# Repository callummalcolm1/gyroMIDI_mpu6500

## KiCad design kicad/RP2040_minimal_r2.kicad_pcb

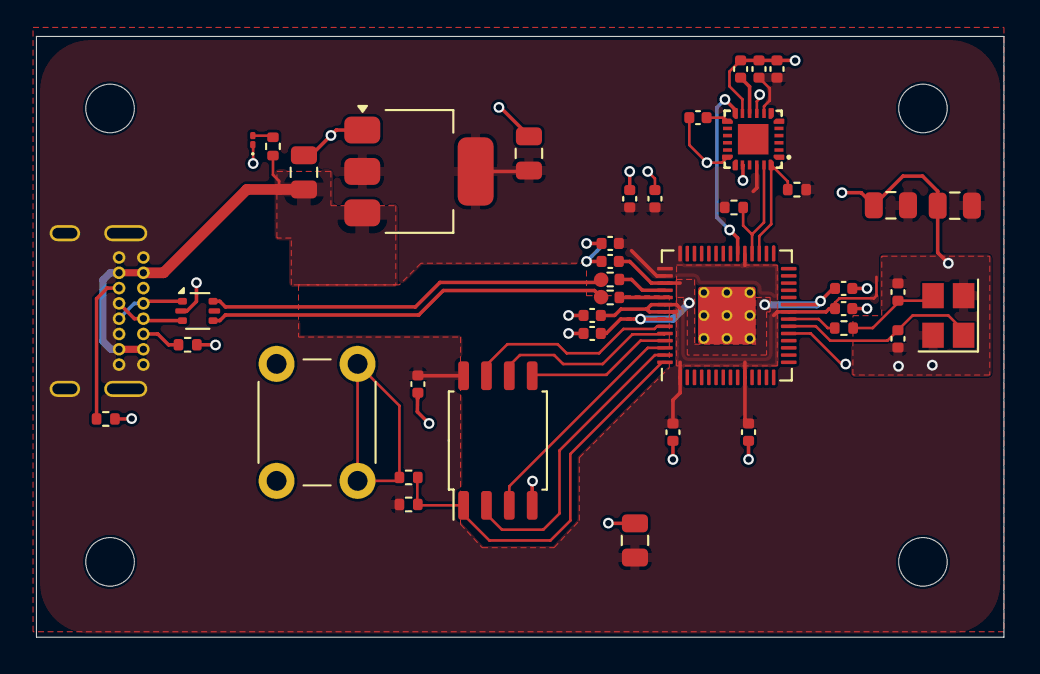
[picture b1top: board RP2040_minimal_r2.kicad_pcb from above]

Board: 2 copper layers, 53.8 x 33.4 mm, 45 parts (1 on the bottom side), 28 nets.

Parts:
C1: 0.1uF; C_0805_2012Metric
C1#2, C5, C6, C7, C9, C11, C12, C13, C14, C15, C16: 100n; C_0402_1005Metric
C2, C3: 15p; C_0402_1005Metric
C4: 2.2uF; C_0805_2012Metric
C4#2, C20: 1uF; C_0402_1005Metric
C8, C10: 1u; C_0402_1005Metric
C17, C18, C19: 10u; C_0805_2012Metric
D1: LED; LED_01005_0402Metric
H1, H2, H3, H4: MountingHole; MountingHole_2.7mm_M2.5
J5: USB_C_Receptacle_USB2.0_16P; USB_C_Receptacle_GCT_USB4085
R1, R5: 1k; R_0402_1005Metric
R2: DNF; R_0402_1005Metric
R3, R4: 27R; R_0402_1005Metric
R6, R7: 5.1K; R_0402_1005Metric
R8, R9: 4.7K; R_0402_1005Metric
R10: R; R_0402_1005Metric
SW1: SW_Push; SW_PUSH_6mm_H4.3mm
U1: MPU6500; QFN-24_L3.0-W3.0-P0.40-BL-EP
U2: W25Q128JVS; SOIC-8_5.23x5.23mm_P1.27mm
U3: RP2040; RP2040-QFN-56
U4: NCP1117-3.3_SOT223; SOT-223-3_TabPin2
U5: USBLC6-2SC6; SOT-666
Y1: ABM8-272-T3; Crystal_SMD_3225-4Pin_3.2x2.5mm

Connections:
+1V1: C6.1, C7.1, C8.1, U3.23 (DVDD), U3.45 (VREG_VOUT), U3.50 (DVDD)
+3V3: C1.1, C1#2.1, C4.1, C5.1, C9.1, C10.1, C11.1, C12.1, C13.1, C14.1, C15.1, C16.1, C17.1, C19.1, R2.1, R8.1, R9.1, U1.8 (VDDIO), U1.22 (nCS), U2.8 (VCC), U3.1 (IOVDD), U3.10 (IOVDD), U3.22 (IOVDD), U3.33 (IOVDD), U3.42 (IOVDD), U3.43 (ADC_AVDD), U3.44 (VREG_IN), U3.48 (USB_VDD), U3.49 (IOVDD), U4.2 (VO)
D+: R3.1, U5.4 (I/O2)
D-: R4.1, U5.6 (I/O1)
GND: C1.2, C1#2.2, C2.2, C3.2, C4.2, C4#2.1, C5.2, C6.2, C7.2, C8.2, C9.2, C10.2, C11.2, C12.2, C13.2, C14.2, C15.2, C16.2, C17.2, C18.2, C19.2, C20.1, D1.1 (K), J5.A1 (GND), J5.A12 (GND), J5.B1 (GND), J5.B12 (GND), J5.S1 (SHIELD), R6.1, R7.1, SW1.1, U1.9 (SDO/AD0), U1.11 (FSYNC), U1.18 (GND), U1.20 (RESV), U2.4 (GND), U3.19 (TESTEN), U3.57 (GND), U4.1 (GND), U5.2 (GND), Y1.2, Y1.4
INT: U1.12 (INT), U3.34 (GPIO22)
unnamed: C3.1, R5.2, Y1.3
unnamed: D1.2 (A), R10.2
unnamed: J5.A5 (CC1), R7.2
unnamed: J5.B5 (CC2), R6.2
unnamed: J5.A6 (D+), J5.B6 (D+), U5.3 (I/O2)
unnamed: J5.A7 (D-), J5.B7 (D-), U5.1 (I/O1)
unnamed: R1.2, SW1.2
unnamed: C20.2, U1.10 (REGOUT)
unnamed: C4#2.2, U1.13 (VDD)
unnamed: R4.2, U3.46 (USB_DM)
unnamed: R3.2, U3.47 (USB_DP)
QSPI_SCLK: U2.6 (CLK), U3.52 (QSPI_SCLK)
QSPI_SD0: U2.5 (DI(IO0)), U3.53 (QSPI_SD0)
QSPI_SD1: U2.2 (DO(IO1)), U3.55 (QSPI_SD1)
QSPI_SD2: U2.3 (IO2), U3.54 (QSPI_SD2)
QSPI_SD3: U2.7 (IO3), U3.51 (QSPI_SD3)
QSPI_SS: R1.1, R2.2, U2.1 (~CS), U3.56 (QSPI_SS)
SCL: R9.2, U1.23 (SCL/SCLK), U3.32 (GPIO21)
SDA: R8.2, U1.24 (SDA/SDI), U3.31 (GPIO20)
VBUS: C18.1, J5.A4 (VBUS), J5.A9 (VBUS), J5.B4 (VBUS), J5.B9 (VBUS), R10.1, U4.3 (VI)
XIN: C2.1, U3.20 (XIN), Y1.1
XOUT: R5.1, U3.21 (XOUT)
